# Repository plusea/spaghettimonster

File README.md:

# spaghettimonster

The spaghettimonster is a tool we developed for playing with wearable technology first, before making it yourself. It is basically a breakout board for an ESP32 Dev Module with six audio sockets connected to pins that have an Analog to Digital Converter (ADC). This allows one to then use audio cables to make electrical connections between the i/o pins of the ESP and textile/wearable sensors mounted around the body or in/on puppets or objects. Spaghettimonster babies are little breakout boards for audio sockets so that one can make connections with conductive thread from the socket to the textile sensor.

### CODE
* [Clock Divider's Spaghetti Monster Firmware](https://github.com/clockdiv/Spaghettimonster)

### LINKS
* [spaghettimonster intro](https://www.kobakant.at/DIY/?p=9137)
* [photos](https://www.flickr.com/photos/plusea/albums/72157719958295195)
* workshops that tested the spaghettimonster v1:
** [sensitive puppetes](https://www.flickr.com/photos/plusea/albums/72157713930789442)
** [communicating bodies]()

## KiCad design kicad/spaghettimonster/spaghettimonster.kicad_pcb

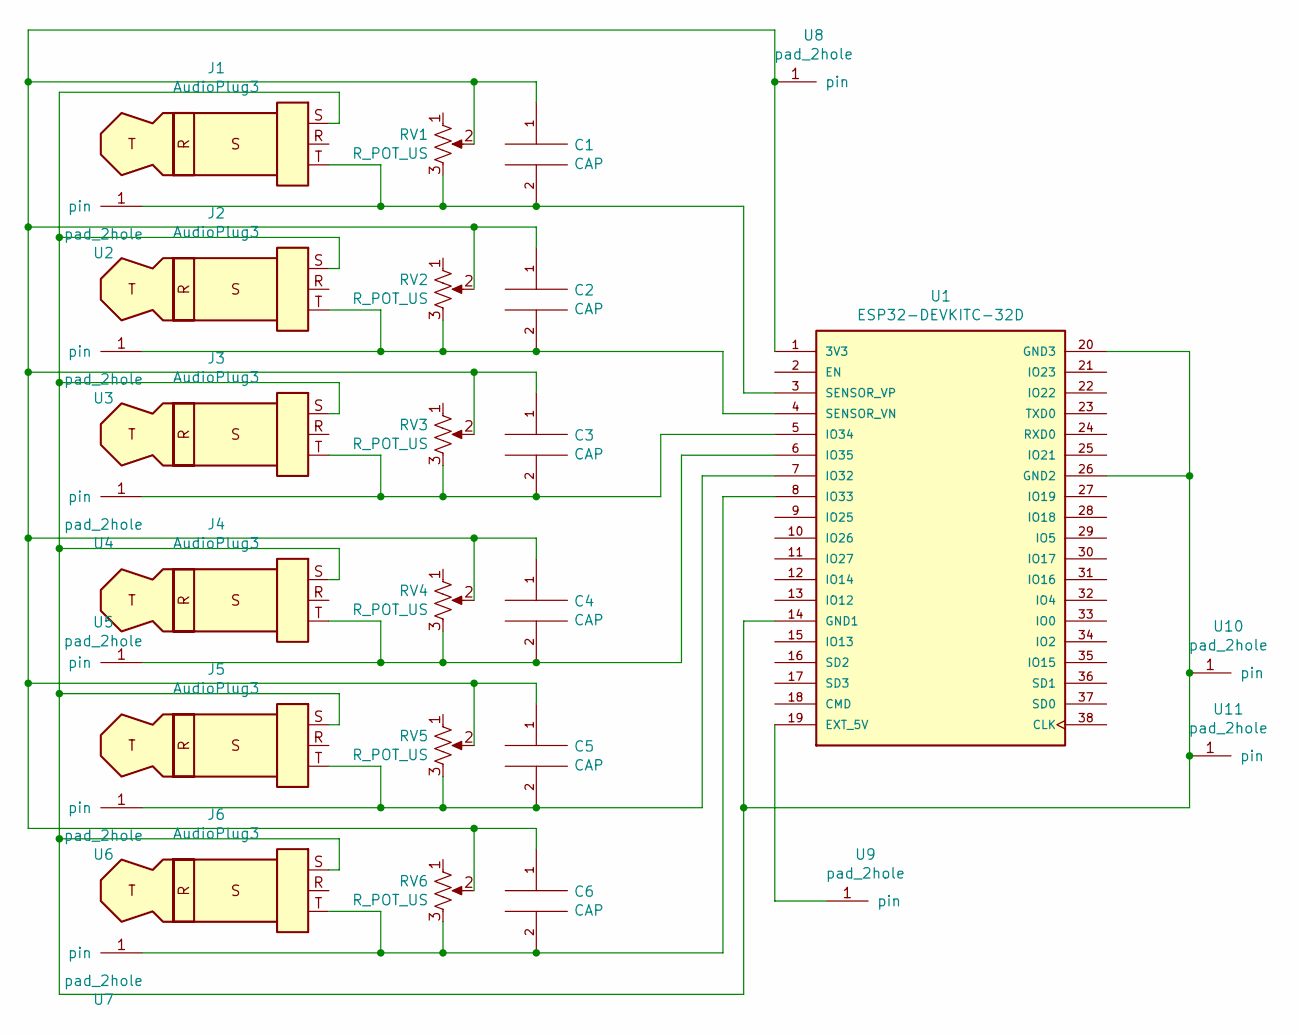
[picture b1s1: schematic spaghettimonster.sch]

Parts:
C1, C2, C3, C4, C5, C6: CAP; CP_Radial_D4.0mm_P2.00mm
J1, J2, J3, J4, J5, J6: AudioPlug3; Jack_3.5mm_Lumberg_1503_07_Horizontal
RV1, RV2, RV3, RV4, RV5, RV6: R_POT_US; Potentiometer_Trimmer_Piher_PT-6v_Horizontal
U1: ESP32-DEVKITC-32D; MODULE_ESP32-DEVKITC-32D; PARTREV 4
U2, U3, U4, U5, U6, U7, U8, U9, U10, U11: pad_2hole; pad_clip-edge-3mm

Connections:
unnamed: C1.1, C2.1, C3.1, C4.1, C5.1, C6.1, RV1.2, RV2.2, RV3.2, RV4.2, RV5.2, RV6.2, U1.1 (3V3), U8.1
unnamed: C1.2, J1.T, RV1.3, U1.3 (SENSOR_VP), U2.1
unnamed: C2.2, J2.T, RV2.3, U1.4 (SENSOR_VN), U3.1
unnamed: C3.2, J3.T, RV3.3, U1.5 (IO34), U4.1
unnamed: C4.2, J4.T, RV4.3, U1.6 (IO35), U5.1
unnamed: C5.2, J5.T, RV5.3, U1.7 (IO32), U6.1
unnamed: C6.2, J6.T, RV6.3, U1.8 (IO33), U7.1
unnamed: J1.S, J2.S, J3.S, J4.S, J5.S, J6.S, U1.14 (GND1), U1.20 (GND3), U1.26 (GND2), U10.1, U11.1
unnamed: U1.19 (EXT_5V), U9.1

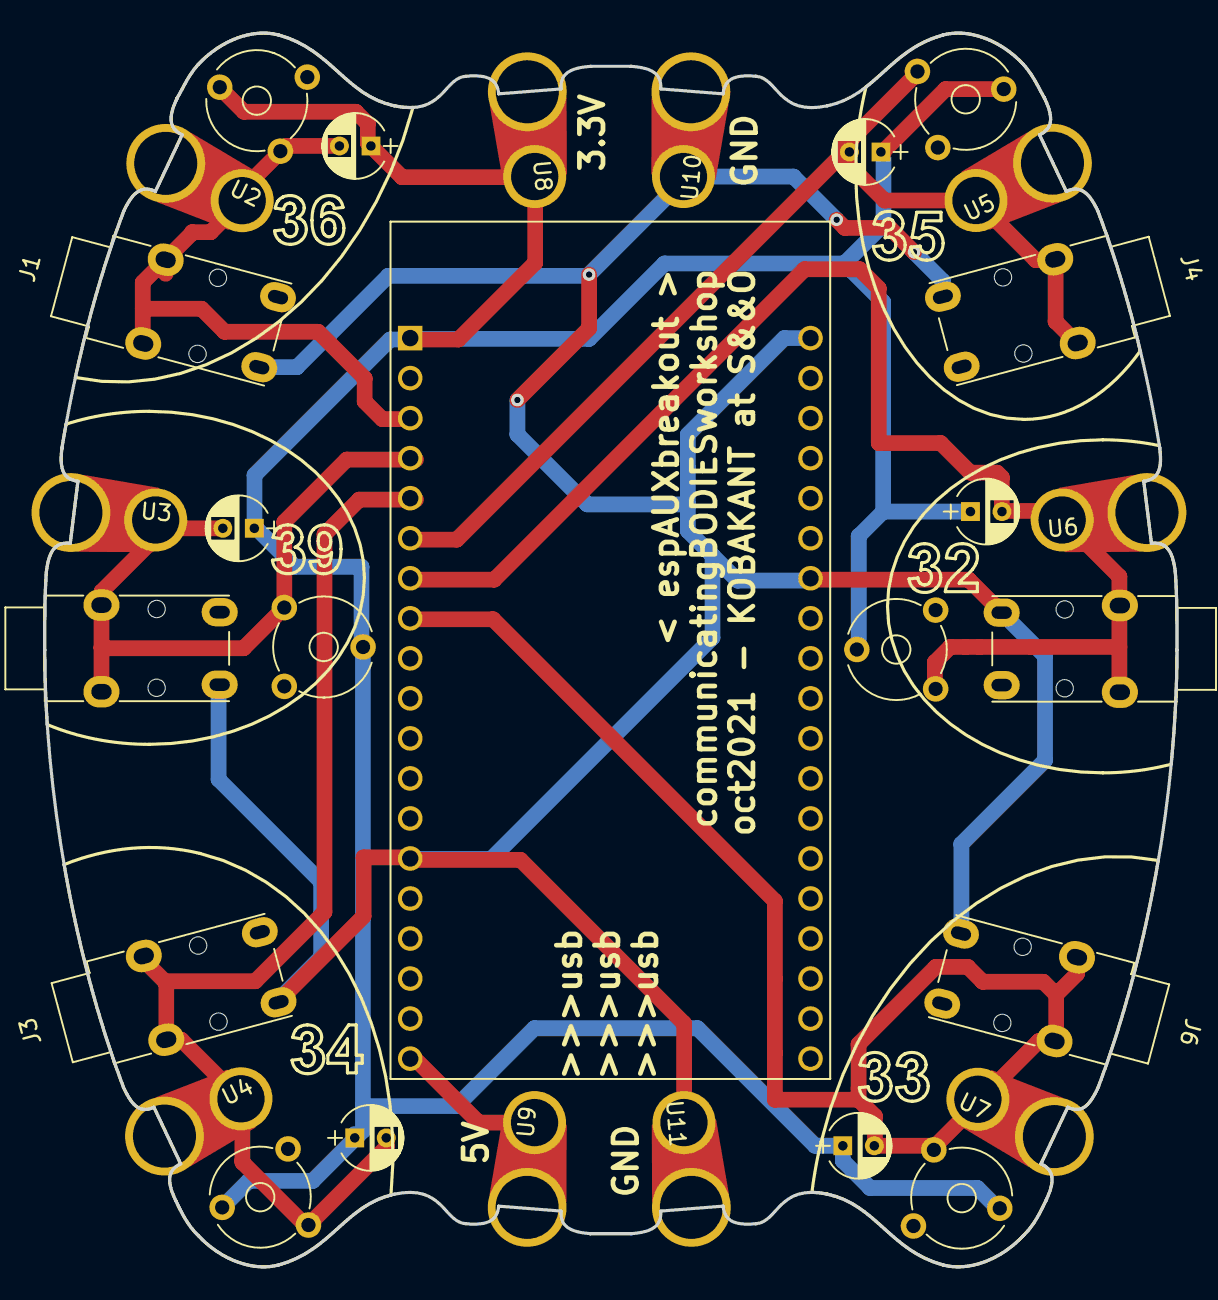
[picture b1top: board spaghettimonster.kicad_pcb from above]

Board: 2 copper layers, 71.8 x 78.3 mm, 29 parts (0 on the bottom side), 9 nets.

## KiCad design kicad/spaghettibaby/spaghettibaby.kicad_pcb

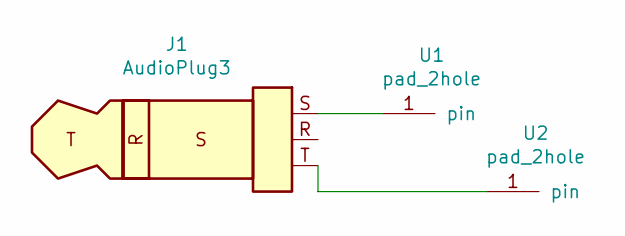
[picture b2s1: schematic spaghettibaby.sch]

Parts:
J1: AudioPlug3; Jack_3.5mm_Lumberg_1503_07_Horizontal
U1, U2: pad_2hole; pad_sew-edge-3x3.5mm

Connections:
unnamed: J1.S, U1.1
unnamed: J1.T, U2.1

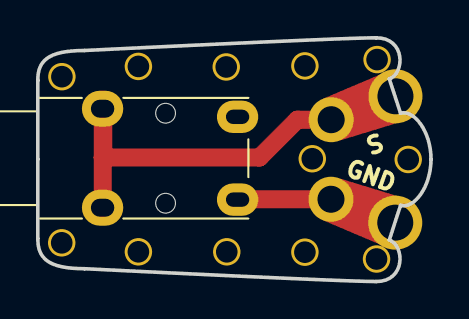
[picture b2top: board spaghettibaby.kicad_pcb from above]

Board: 2 copper layers, 21.8 x 13.5 mm, 3 parts (0 on the bottom side), 2 nets.

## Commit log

2022-06-10 adding
2022-06-10 adding kicad files
